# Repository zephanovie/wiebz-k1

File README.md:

# WIEBZ-K1
The Beginning of a new brand...WIEBZ (Willed Into Existence By Zephan).....its a 60% keyboard with a cool design (i hope)
it uses a raspberry pi pico as the MCU, the switches would be hot swappable. it has a daisy chain of SK6812 mini-e leds that would be both bottom mounted for the per key led and top mounted that would serve as the ambient lights around three corners of the keyboard...and it would be running the qmk firmware. The PCB was designed in KiCad, the case in Fusion 

# Features <br><br>
- Rp2040 controller
- per-key led
- a 60% layout
- under glow lights
- qmk firmware

# BOM

| Item                          | Qty       | Price (₦)              | Price($)           | Source                                                                                                                                                                                                                                                                                                                                                                                                                                                                                                                                                                                                                                                                                                                                                               | 
| :---------------------------- | :-------- | :--------------------- | :----------------- | :------------------------------------------------------------------------------------------------------------------------------------------------------------------------------------------------------------------------------------------------------------------------------------------------------------------------------------------------------------------------------------------------------------------------------------------------------------------------------------------------------------------------------------------------------------------------------------------------------------------------------------------------------------------------------------------------------------------------------------------------------------------- | 
| PCB                           | 5         | 48,964.14              | 36.87 (W Shipping) | JLCPCB                                                                                                                                                                                                                                                                                                                                                                                                                                                                                                                                                                                                                                                                                                                                                               | 
| Raspberry Pi Pico W           | 1         | 23,000                 | 17.32              | https://hub360.cc/shop/0408-raspberry-pi-pico-w-rp2040-type-c-dual-core-microcontroller-development-board-12216                                                                                                                                                                                                                                                                                                                                                                                                                                                                                                                                                                                                                                                      | 
| Kailh Hotswappable MX Sockets | 70        | 8,237                  | 6.2                | https://www.aliexpress.com/item/1005012011087592.html?spm=a2g0o.productlist.main.19.23687332bLHZxK&algo_pvid=e4fd706c-1c1c-4431-b9ec-5773bd71d8b5&algo_exp_id=e4fd706c-1c1c-4431-b9ec-5773bd71d8b5-18&pdp_ext_f=%7B%22order%22%3A%223368%22%2C%22eval%22%3A%221%22%2C%22orig_sl_item_id%22%3A%221005012011087592%22%2C%22orig_item_id%22%3A%221005009794038277%22%2C%22fromPage%22%3A%22search%22%7D&pdp_npi=6%40dis%21NGN%2116474.42%218237.00%21%21%2173.78%2136.89%21%40214134eb17905273223806978e0c4b%2112000057272683072%21sea%21NG%217964375220%21X%211%210%21n_tag%3A-29911%3Bd%3Af57d49e4%3Bm03_new_user%3A-29895&curPageLogUid=ZSE8mI1xv3yo&utparam-url=scene%3Asearch%7Cquery_from%3A%7Cx_object_id%3A1005012011087592%7C_p_origin_prod%3A1005009794038277 | 
| MX Mechanical Switches        | 70 (10*7) | 22,967.57 (W Shipping) | 17.29              | https://www.aliexpress.com/item/1005003206504286.html?spm=a2g0o.productlist.main.3.b8f41654VLycgA&algo_pvid=f2801b0d-82a7-46ab-8a0e-5c219dedf416&algo_exp_id=f2801b0d-82a7-46ab-8a0e-5c219dedf416-2&pdp_ext_f=%7B%22order%22%3A%22182%22%2C%22spu_best_type%22%3A%22price%22%2C%22eval%22%3A%221%22%2C%22fromPage%22%3A%22search%22%7D&pdp_npi=6%40dis%21NGN%213192.96%212267.00%21%21%2114.30%2110.15%21%400b08c0c217905277692458720e0f04%2112000024658535533%21sea%21NG%217964375220%21X%211%210%21n_tag%3A-29911%3Bd%3Af57d49e4%3Bm03_new_user%3A-29895&curPageLogUid=cNFM0hmjKg5j&utparam-url=scene%3Asearch%7Cquery_from%3A%7Cx_object_id%3A1005003206504286%7C_p_origin_prod%3A                                                                                | 
| 1N4148 THT Diodes             | 100       | 2,207                  | 1.66               | https://www.aliexpress.com/item/4001126137167.html?spm=a2g0o.productlist.main.2.4cfb37b6KyUXtS&algo_pvid=093f6531-d1bc-4cf5-8007-ee3db067eeed&algo_exp_id=093f6531-d1bc-4cf5-8007-ee3db067eeed-1&pdp_ext_f=%7B%22order%22%3A%222116%22%2C%22spu_best_type%22%3A%22price%22%2C%22eval%22%3A%221%22%2C%22fromPage%22%3A%22search%22%7D&pdp_npi=6%40dis%21NGN%212207.00%212207.00%21%21%211.47%211.47%21%402141397017905286836131318e0ca7%2110000014629985518%21sea%21NG%217964375220%21X%211%210%21n_tag%3A-29911%3Bd%3Af57d49e4%3Bm03_new_user%3A-29895&curPageLogUid=Fgjax7A3c4sT&utparam-url=scene%3Asearch%7Cquery_from%3A%7Cx_object_id%3A4001126137167%7C_p_origin_prod%3A                                                                                       | 
| Stabilizers                   | 5         | 14,321                 | 10.78              | https://www.aliexpress.com/item/4001143514438.html?spm=a2g0o.productlist.main.1.180c40f0HGmRfm&algo_pvid=68c55ac8-eff4-44c4-b19f-65739acc819b&algo_exp_id=68c55ac8-eff4-44c4-b19f-65739acc819b-0&pdp_ext_f=%7B%22order%22%3A%22129%22%2C%22eval%22%3A%221%22%2C%22fromPage%22%3A%22search%22%7D&pdp_npi=6%40dis%21NGN%2113616.00%2113616.00%21%21%219.07%219.07%21%402141137e17905299800648528e0ea6%2112000033301894112%21sea%21NG%217964375220%21X%211%210%21n_tag%3A-29911%3Bd%3Af57d49e4%3Bm03_new_user%3A-29895&curPageLogUid=hGLGjyTulFV4&utparam-url=scene%3Asearch%7Cquery_from%3A%7Cx_object_id%3A4001143514438%7C_p_origin_prod%3A                                                                                                                          | 
| SK6812 MINI-E leds            | 100       | 5,224                  | 3.93               | https://www.aliexpress.com/item/1005007863635868.html?spm=a2g0o.productlist.main.6.14c8547fFrwORl&algo_pvid=d5345fc8-f421-434d-a9b3-912494c1ab0e&algo_exp_id=d5345fc8-f421-434d-a9b3-912494c1ab0e-5&pdp_ext_f=%7B%22order%22%3A%22644%22%2C%22eval%22%3A%221%22%2C%22fromPage%22%3A%22search%22%7D&pdp_npi=6%40dis%21NGN%215224.00%215224.00%21%21%213.48%213.48%21%4021410daa17905379482431718e0f31%2112000042594617264%21sea%21NG%217964375220%21X%211%210%21n_tag%3A-29911%3Bd%3Af57d49e4%3Bm03_new_user%3A-29895&curPageLogUid=zBx0bm7r2RNj&utparam-url=scene%3Asearch%7Cquery_from%3A%7Cx_object_id%3A1005007863635868%7C_p_origin_prod%3A                                                                                                                      | 
| Screws                        | 0         | 0                      | 0                  | Self-Covered                                                                                                                                                                                                                                                                                                                                                                                                                                                                                                                                                                                                                                                                                                                                                         | 
| Heat Inserts                  | 0         | 0                      | 0                  | Self-Covered                                                                                                                                                                                                                                                                                                                                                                                                                                                                                                                                                                                                                                                                                                                                                         | 
| Key Caps                      | 133 keys  | 19,885                 | 14.97              | https://www.aliexpress.com/item/1005009592262575.html?spm=a2g0o.productlist.main.2.711f3e457cKNiY&algo_pvid=7fbda4a7-b7a8-44b1-97d1-95525804c150&algo_exp_id=7fbda4a7-b7a8-44b1-97d1-95525804c150-1&pdp_ext_f=%7B%22order%22%3A%22369%22%2C%22spu_best_type%22%3A%22price%22%2C%22eval%22%3A%221%22%2C%22fromPage%22%3A%22search%22%7D&pdp_npi=6%40dis%21NGN%2141427.08%2119885.00%21%21%21185.52%2189.05%21%400be71e1917905404057533196e0c73%2112000049561056701%21sea%21NG%217964375220%21X%211%210%21n_tag%3A-29911%3Bd%3Af57d49e4%3Bm03_new_user%3A-29895&curPageLogUid=Qs7ffMCvOio6&utparam-url=scene%3Asearch%7Cquery_from%3A%7Cx_object_id%3A1005009592262575%7C_p_origin_prod%3A                                                                             | 
| TOTAL                         |           | 121,838.14             | 72.15              |                                                                                                                                                                                                                                                                                                                                                                                                                                                                                                                                                                                                                                                                                                                                                                      | 

# Images
## Schematics
#### Keyboard Matrix

#### LED Chain

#### MCU

## PCB
#### PCB Design

#### PCB 3D Render

## Case
#### Plate

#### Base

### MCU Cover
 (to be glue to the plate after printing)

#### Full Case

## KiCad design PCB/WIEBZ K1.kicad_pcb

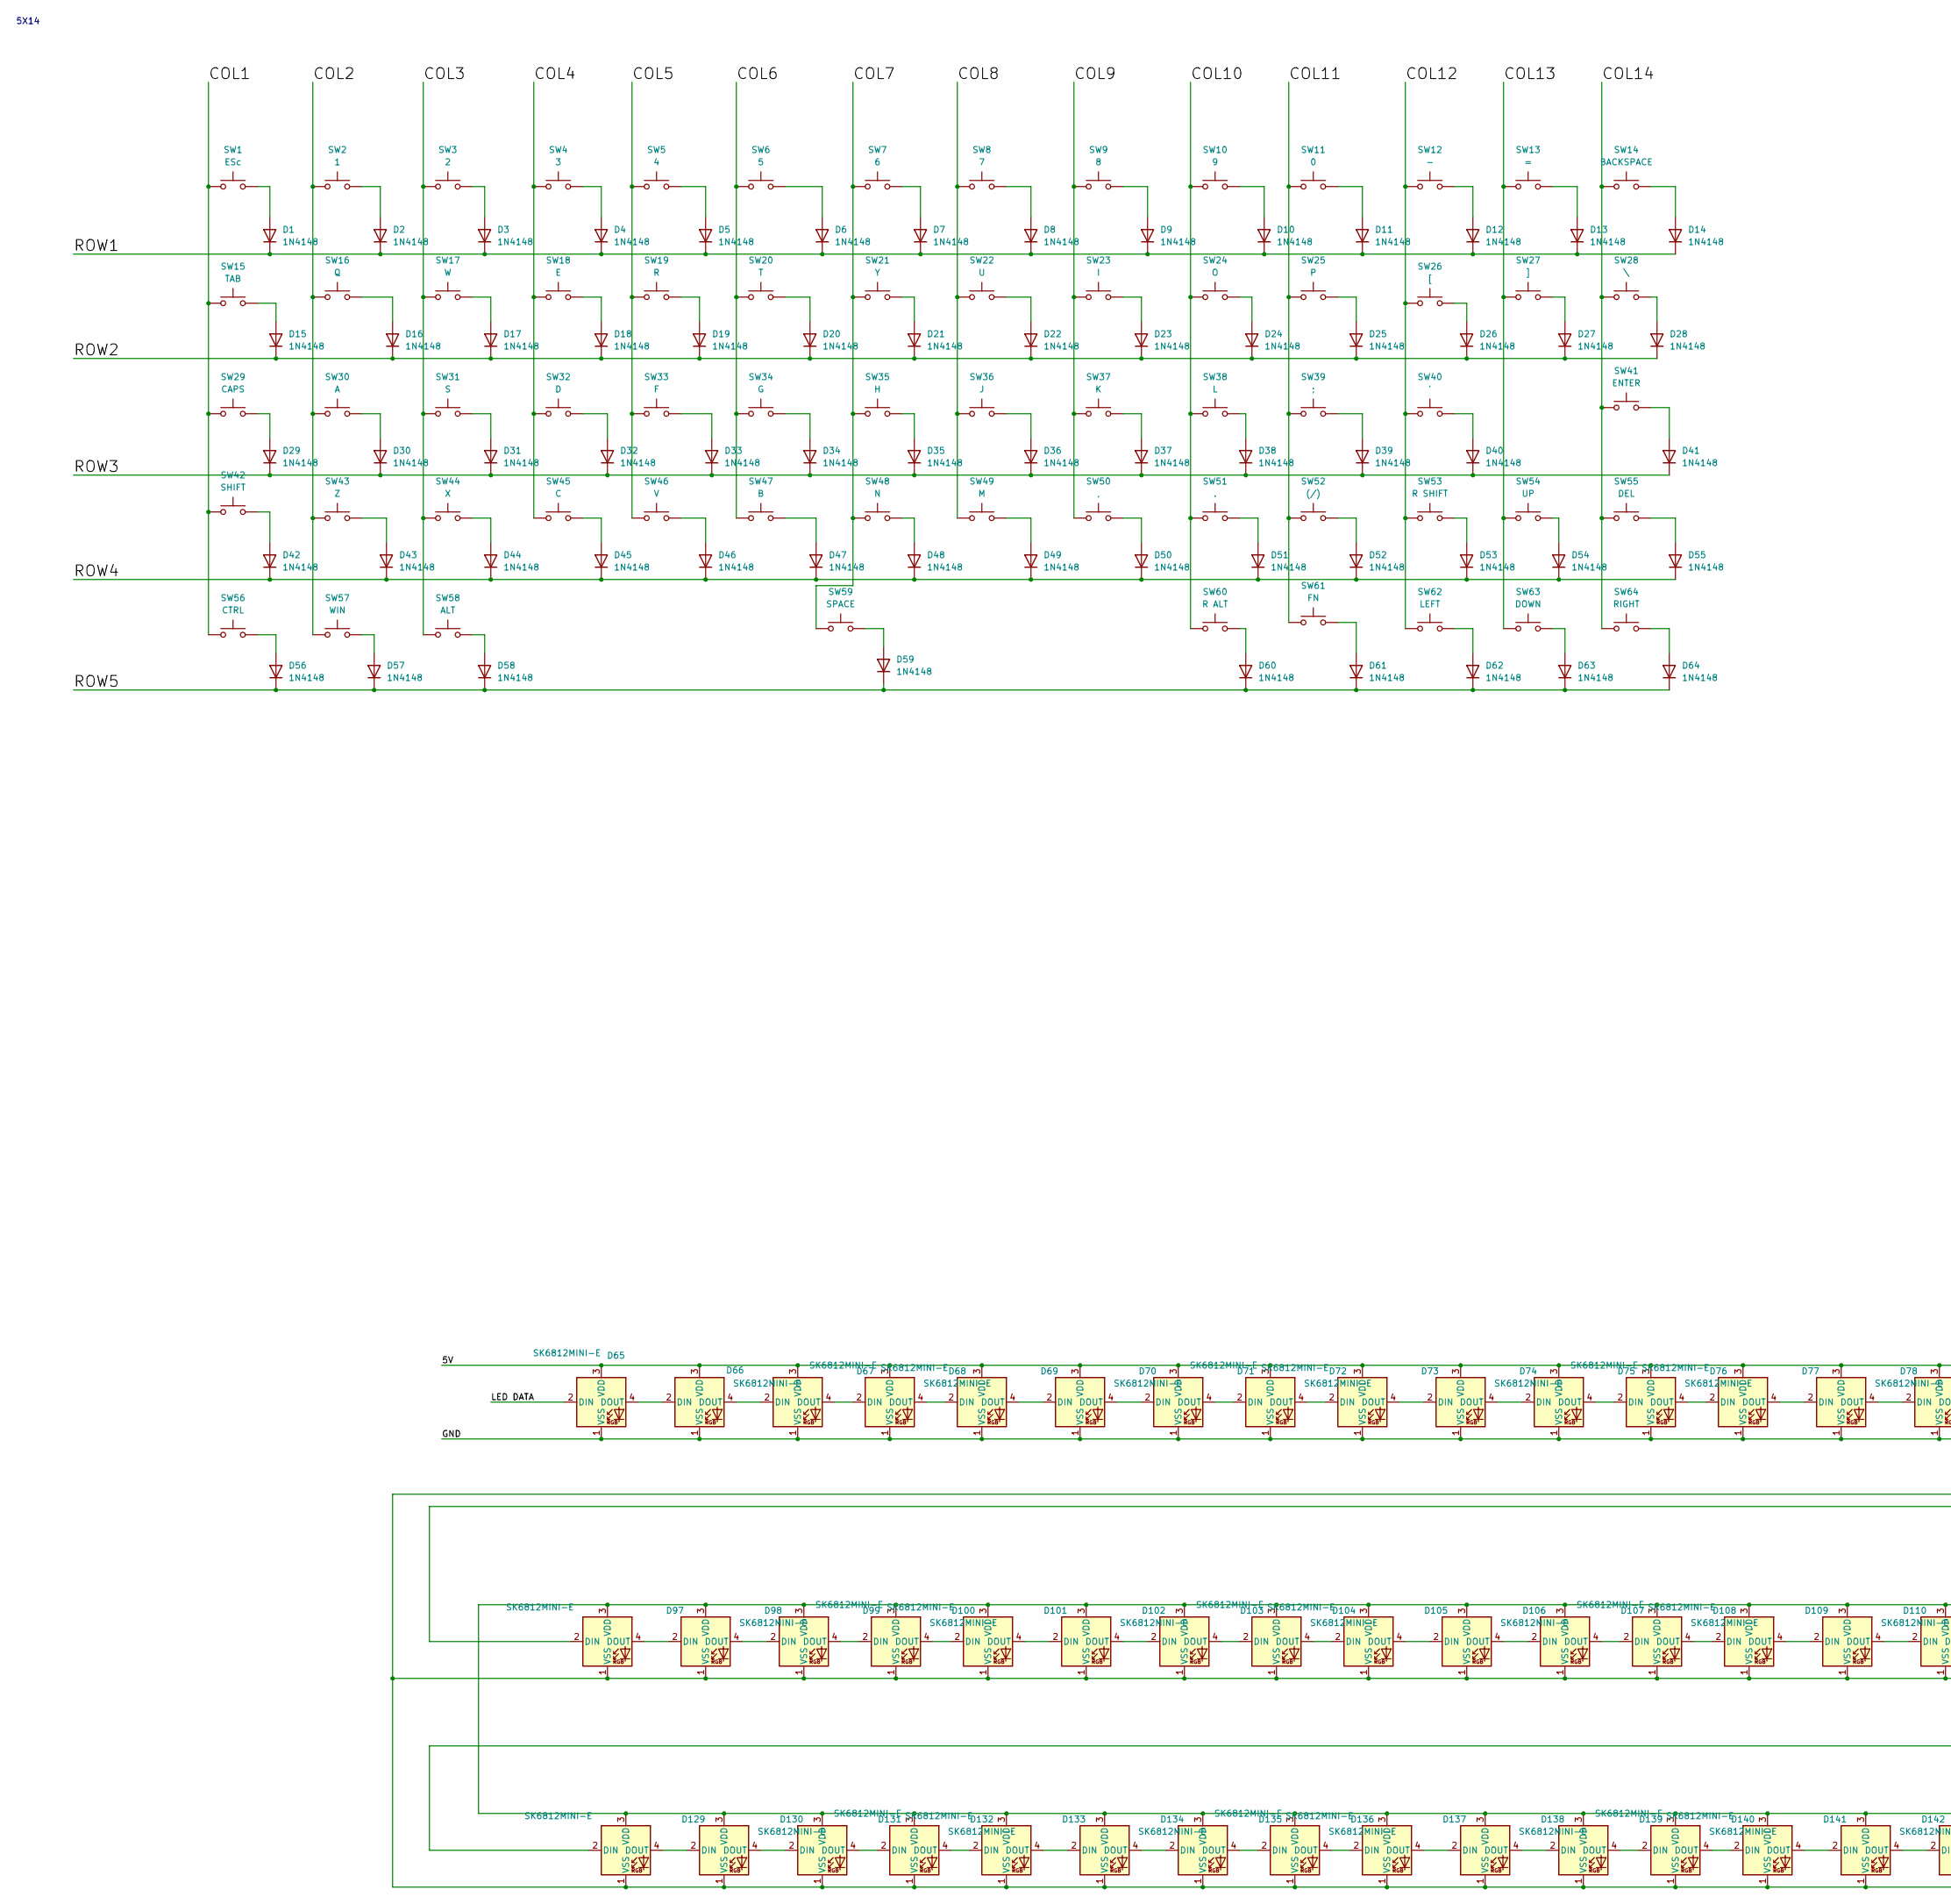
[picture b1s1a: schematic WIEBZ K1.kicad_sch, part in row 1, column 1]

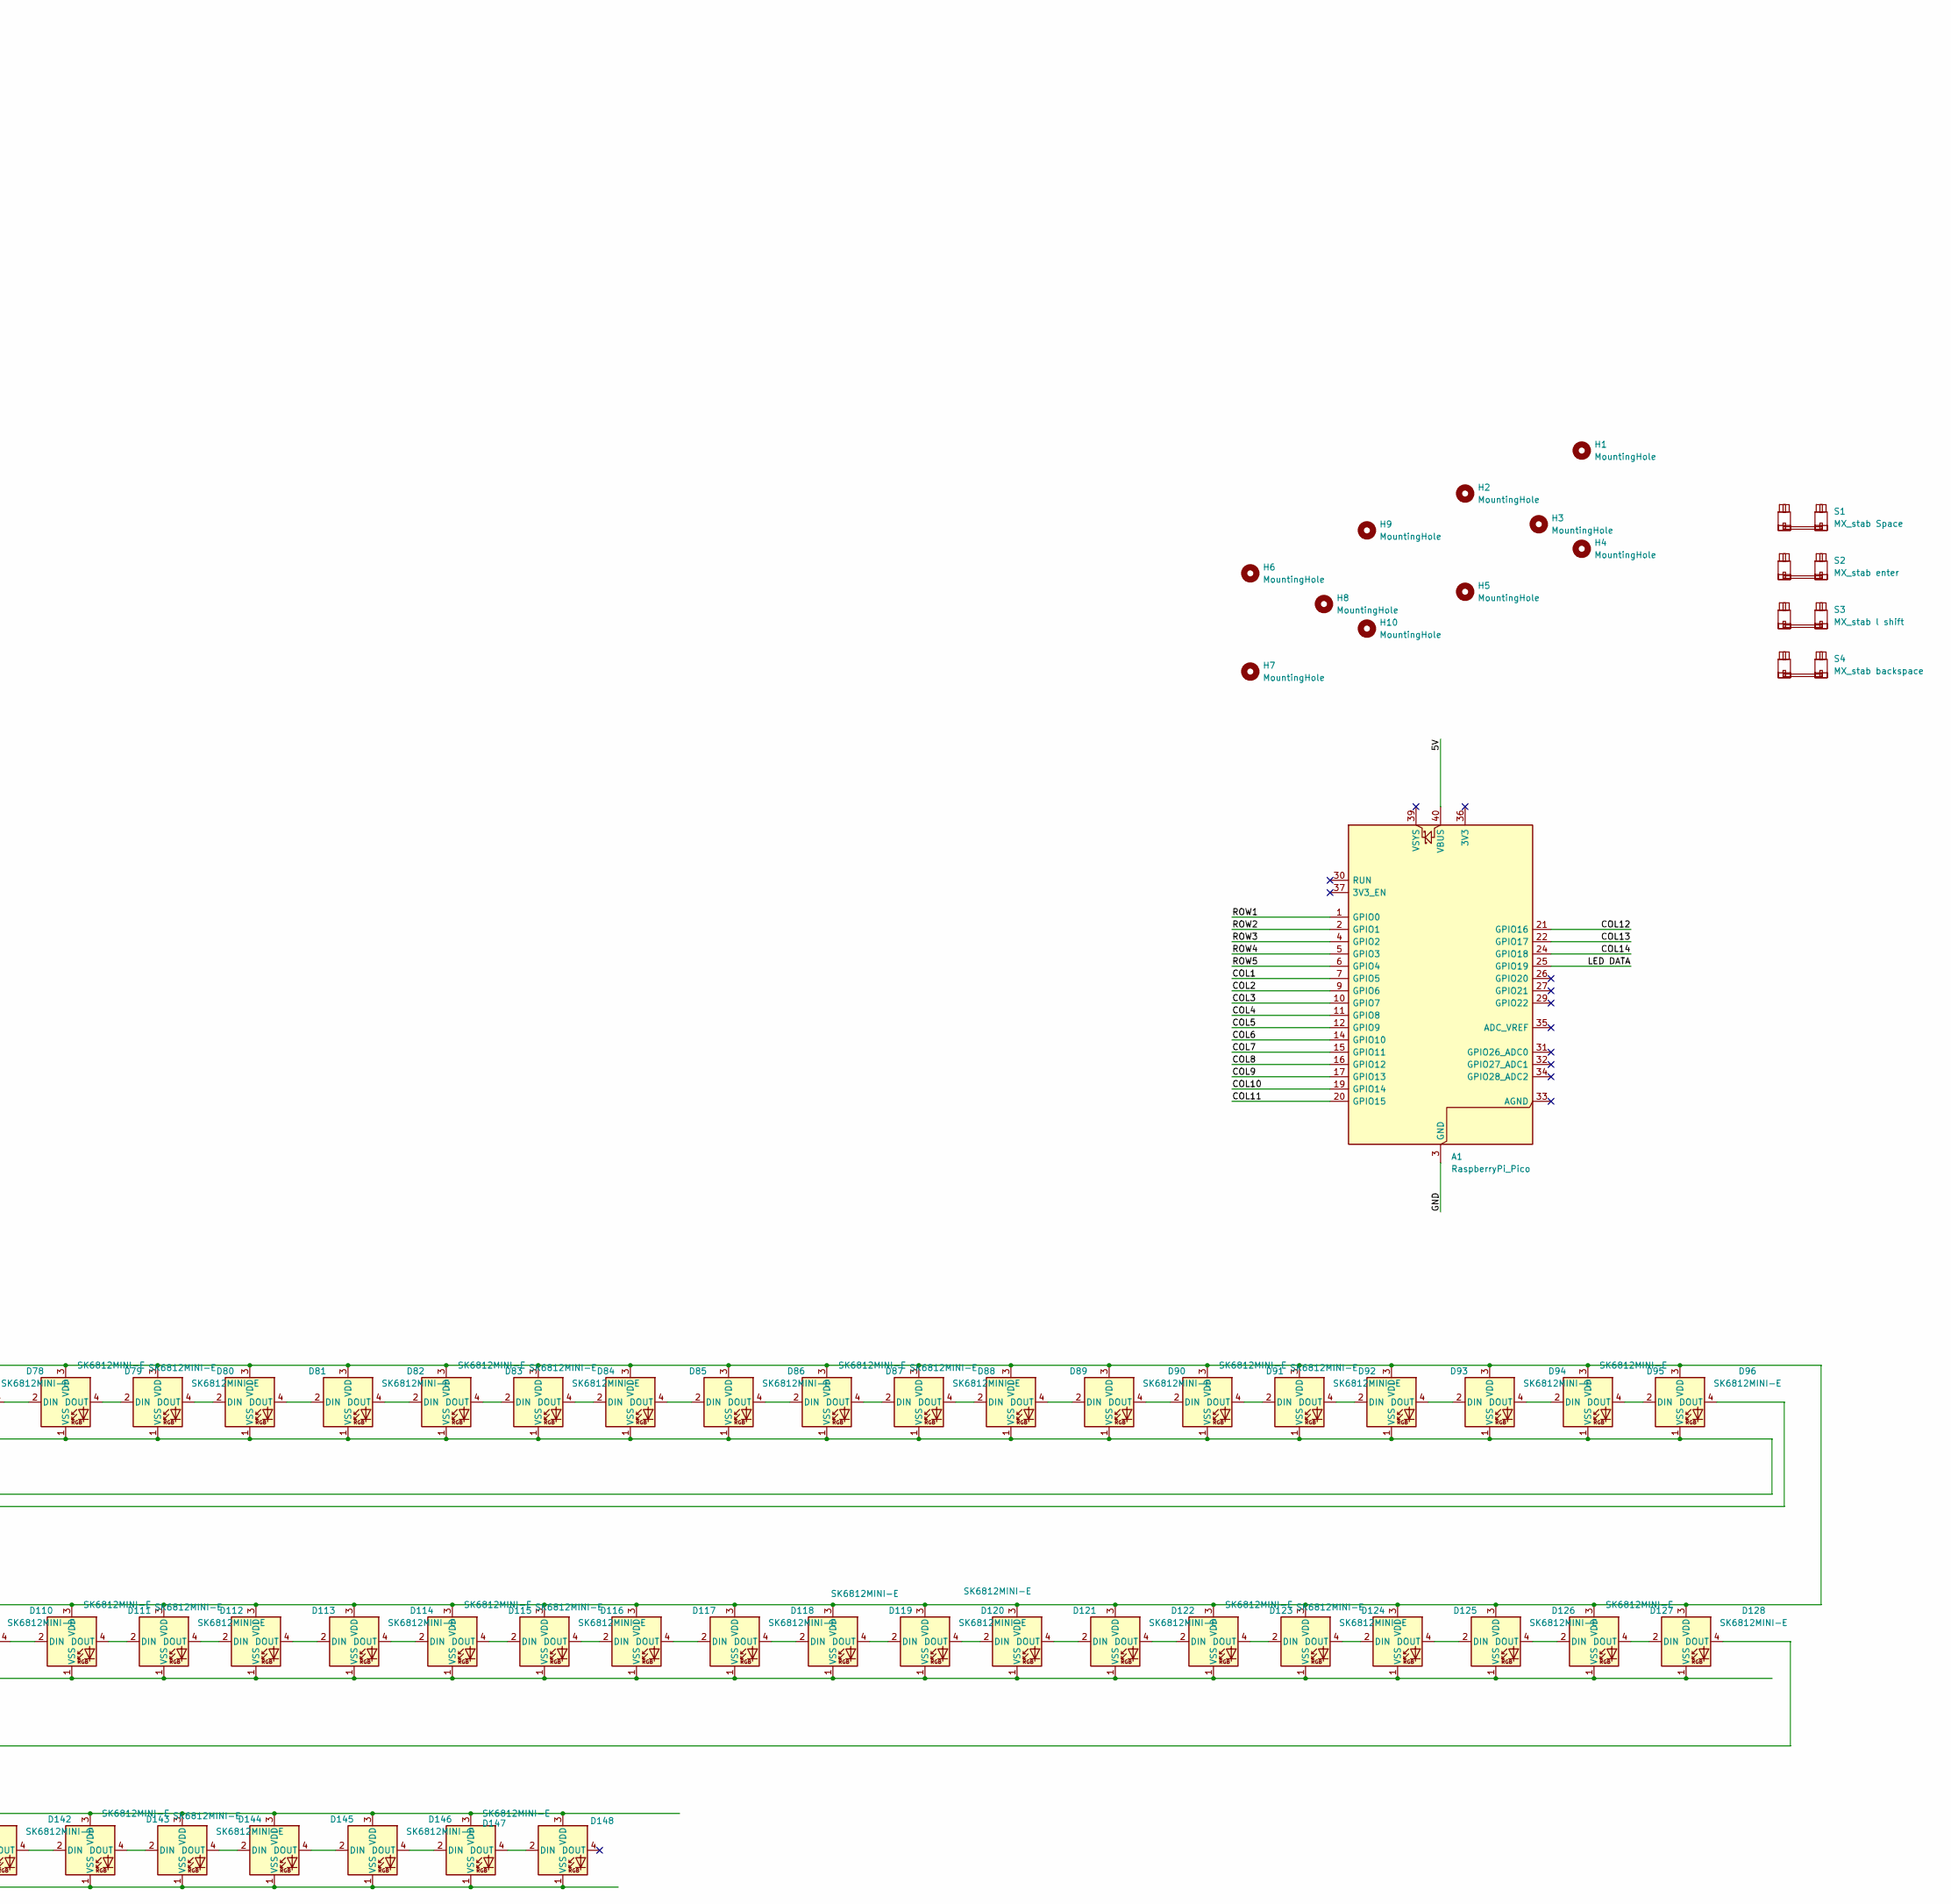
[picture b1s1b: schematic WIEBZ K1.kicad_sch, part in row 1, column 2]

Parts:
A1: RaspberryPi_Pico; RaspberryPi_Pico_Common_THT
D1, D2, D3, D4, D5, D6, D7, D8, D9, D10, D11, D12, D13, D14, D15, D16, D17, D18, D19, D20, D21, D22, D23, D24, D25, D26, D27, D28, D29, D30, D31, D32, D33, D34, D35, D36, D37, D38, D39, D40, D41, D42, D43, D44, D45, D46, D47, D48, D49, D50, D51, D52, D53, D54, D55, D56, D57, D58, D59, D60, D61, D62, D63, D64: 1N4148; D_DO-35_SOD27_P7.62mm_Horizontal
D65, D66, D67, D68, D69, D70, D71, D72, D73, D74, D75, D76, D77, D78, D79, D80, D81, D82, D83, D84, D85, D86, D87, D88, D89, D90, D91, D92, D93, D94, D95, D96, D97, D98, D99, D100, D101, D102, D103, D104, D105, D106, D107, D108, D109, D110, D111, D112, D113, D114, D115, D116, D117, D118, D119, D120, D121, D122, D123, D124, D125, D126, D127, D128, D129, D130, D131, D132, D133, D134, D135, D136, D137, D138, D139, D140, D141, D142, D143, D144, D145, D146, D147, D148: SK6812MINI-E; LED_SK6812MINI-E_3.2x2.8mm_P1.5mm_ReverseMount
H1, H2, H3, H4, H5, H6, H7, H8, H9, H10: MountingHole; MountingHole_3.2mm_M3
S1: MX_stab Space; STAB_MX_6.25u
S2: MX_stab enter; STAB_MX_2.25u
S3: MX_stab l shift; STAB_MX_2u
S4: MX_stab backspace; STAB_MX_2u
SW1: ESc; SW_Hotswap_Kailh_MX_1.00u_No_silk
SW2: 1; SW_Hotswap_Kailh_MX_1.00u_No_silk
SW3: 2; SW_Hotswap_Kailh_MX_1.00u_No_silk
SW4: 3; SW_Hotswap_Kailh_MX_1.00u_No_silk
SW5: 4; SW_Hotswap_Kailh_MX_1.00u_No_silk
SW6: 5; SW_Hotswap_Kailh_MX_1.00u_No_silk
SW7: 6; SW_Hotswap_Kailh_MX_1.00u_No_silk
SW8: 7; SW_Hotswap_Kailh_MX_1.00u_No_silk
SW9: 8; SW_Hotswap_Kailh_MX_1.00u_No_silk
SW10: 9; SW_Hotswap_Kailh_MX_1.00u_No_silk
SW11: 0; SW_Hotswap_Kailh_MX_1.00u_No_silk
SW12: -; SW_Hotswap_Kailh_MX_1.00u_No_silk
SW13: =; SW_Hotswap_Kailh_MX_1.00u_No_silk
SW14: BACKSPACE; SW_Hotswap_Kailh_MX_1.00u_No_silk
SW15: TAB; SW_Hotswap_Kailh_MX_1.00u_No_silk
SW16: Q; SW_Hotswap_Kailh_MX_1.00u_No_silk
SW17: W; SW_Hotswap_Kailh_MX_1.00u_No_silk
SW18: E; SW_Hotswap_Kailh_MX_1.00u_No_silk
SW19: R; SW_Hotswap_Kailh_MX_1.00u_No_silk
SW20: T; SW_Hotswap_Kailh_MX_1.00u_No_silk
SW21: Y; SW_Hotswap_Kailh_MX_1.00u_No_silk
SW22: U; SW_Hotswap_Kailh_MX_1.00u_No_silk
SW23: I; SW_Hotswap_Kailh_MX_1.00u_No_silk
SW24: O; SW_Hotswap_Kailh_MX_1.00u_No_silk
SW25: P; SW_Hotswap_Kailh_MX_1.00u_No_silk
SW26: [; SW_Hotswap_Kailh_MX_1.00u_No_silk
SW27: ]; SW_Hotswap_Kailh_MX_1.00u_No_silk
SW28: \; SW_Hotswap_Kailh_MX_1.00u_No_silk
SW29: CAPS; SW_Hotswap_Kailh_MX_1.00u_No_silk
SW30: A; SW_Hotswap_Kailh_MX_1.00u_No_silk
SW31: S; SW_Hotswap_Kailh_MX_1.00u_No_silk
SW32: D; SW_Hotswap_Kailh_MX_1.00u_No_silk
SW33: F; SW_Hotswap_Kailh_MX_1.00u_No_silk
SW34: G; SW_Hotswap_Kailh_MX_1.00u_No_silk
SW35: H; SW_Hotswap_Kailh_MX_1.00u_No_silk
SW36: J; SW_Hotswap_Kailh_MX_1.00u_No_silk
SW37: K; SW_Hotswap_Kailh_MX_1.00u_No_silk
SW38: L; SW_Hotswap_Kailh_MX_1.00u_No_silk
SW39: ;; SW_Hotswap_Kailh_MX_1.00u_No_silk
SW40: '; SW_Hotswap_Kailh_MX_1.00u_No_silk
SW41: ENTER; SW_Hotswap_Kailh_MX_1.00u_No_silk
SW42: SHIFT; SW_Hotswap_Kailh_MX_1.00u_No_silk
SW43: Z; SW_Hotswap_Kailh_MX_1.00u_No_silk
SW44: X; SW_Hotswap_Kailh_MX_1.00u_No_silk
SW45: C; SW_Hotswap_Kailh_MX_1.00u_No_silk
SW46: V; SW_Hotswap_Kailh_MX_1.00u_No_silk
SW47: B; SW_Hotswap_Kailh_MX_1.00u_No_silk
SW48: N; SW_Hotswap_Kailh_MX_1.00u_No_silk
SW49: M; SW_Hotswap_Kailh_MX_1.00u_No_silk
SW50: ,; SW_Hotswap_Kailh_MX_1.00u_No_silk
SW51: .; SW_Hotswap_Kailh_MX_1.00u_No_silk
SW52: (/); SW_Hotswap_Kailh_MX_1.00u_No_silk
SW53: R SHIFT; SW_Hotswap_Kailh_MX_1.00u_No_silk
SW54: UP; SW_Hotswap_Kailh_MX_1.00u_No_silk
SW55: DEL; SW_Hotswap_Kailh_MX_1.00u_No_silk
SW56: CTRL; SW_Hotswap_Kailh_MX_1.00u_No_silk
SW57: WIN; SW_Hotswap_Kailh_MX_1.00u_No_silk
SW58: ALT; SW_Hotswap_Kailh_MX_1.00u_No_silk
SW59: SPACE; SW_Hotswap_Kailh_MX_1.00u_No_silk
SW60: R ALT; SW_Hotswap_Kailh_MX_1.00u_No_silk
SW61: FN; SW_Hotswap_Kailh_MX_1.00u_No_silk
SW62: LEFT; SW_Hotswap_Kailh_MX_1.00u_No_silk
SW63: DOWN; SW_Hotswap_Kailh_MX_1.00u_No_silk
SW64: RIGHT; SW_Hotswap_Kailh_MX_1.00u_No_silk

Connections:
/5V: A1.40 (VBUS), D65.3 (VDD), D66.3 (VDD), D67.3 (VDD), D68.3 (VDD), D69.3 (VDD), D70.3 (VDD), D71.3 (VDD), D72.3 (VDD), D73.3 (VDD), D74.3 (VDD), D75.3 (VDD), D76.3 (VDD), D77.3 (VDD), D78.3 (VDD), D79.3 (VDD), D80.3 (VDD), D81.3 (VDD), D82.3 (VDD), D83.3 (VDD), D84.3 (VDD), D85.3 (VDD), D86.3 (VDD), D87.3 (VDD), D88.3 (VDD), D89.3 (VDD), D90.3 (VDD), D91.3 (VDD), D92.3 (VDD), D93.3 (VDD), D94.3 (VDD), D95.3 (VDD), D96.3 (VDD), D97.3 (VDD), D98.3 (VDD), D99.3 (VDD), D100.3 (VDD), D101.3 (VDD), D102.3 (VDD), D103.3 (VDD), D104.3 (VDD), D105.3 (VDD), D106.3 (VDD), D107.3 (VDD), D108.3 (VDD), D109.3 (VDD), D110.3 (VDD), D111.3 (VDD), D112.3 (VDD), D113.3 (VDD), D114.3 (VDD), D115.3 (VDD), D116.3 (VDD), D117.3 (VDD), D118.3 (VDD), D119.3 (VDD), D120.3 (VDD), D121.3 (VDD), D122.3 (VDD), D123.3 (VDD), D124.3 (VDD), D125.3 (VDD), D126.3 (VDD), D127.3 (VDD), D128.3 (VDD), D129.3 (VDD), D130.3 (VDD), D131.3 (VDD), D132.3 (VDD), D133.3 (VDD), D134.3 (VDD), D135.3 (VDD), D136.3 (VDD), D137.3 (VDD), D138.3 (VDD), D139.3 (VDD), D140.3 (VDD), D141.3 (VDD), D142.3 (VDD), D143.3 (VDD), D144.3 (VDD), D145.3 (VDD), D146.3 (VDD), D147.3 (VDD), D148.3 (VDD)
/COL1: A1.7 (GPIO5), SW1.1, SW15.1, SW29.1, SW42.1, SW56.1
/COL2: A1.9 (GPIO6), SW2.1, SW16.1, SW30.1, SW43.1, SW57.1
/COL3: A1.10 (GPIO7), SW3.1, SW17.1, SW31.1, SW44.1, SW58.1
/COL4: A1.11 (GPIO8), SW4.1, SW18.1, SW32.1, SW45.1
/COL5: A1.12 (GPIO9), SW5.1, SW19.1, SW33.1, SW46.1
/COL6: A1.14 (GPIO10), SW6.1, SW20.1, SW34.1, SW47.1
/COL7: A1.15 (GPIO11), SW7.1, SW21.1, SW35.1, SW48.1, SW59.1
/COL8: A1.16 (GPIO12), SW8.1, SW22.1, SW36.1, SW49.1
/COL9: A1.17 (GPIO13), SW9.1, SW23.1, SW37.1, SW50.1
/COL10: A1.19 (GPIO14), SW10.1, SW24.1, SW38.1, SW51.1, SW60.1
/COL11: A1.20 (GPIO15), SW11.1, SW25.1, SW39.1, SW52.1, SW61.1
/COL12: A1.21 (GPIO16), SW12.1, SW26.1, SW40.1, SW53.1, SW62.1
/COL13: A1.22 (GPIO17), SW13.1, SW27.1, SW54.1, SW63.1
/COL14: A1.24 (GPIO18), SW14.1, SW28.1, SW41.1, SW55.1, SW64.1
/GND: A1.3 (GND), A1.8 (GND), A1.13 (GND), A1.18 (GND), A1.23 (GND), A1.28 (GND), A1.38 (GND), D65.1 (VSS), D66.1 (VSS), D67.1 (VSS), D68.1 (VSS), D69.1 (VSS), D70.1 (VSS), D71.1 (VSS), D72.1 (VSS), D73.1 (VSS), D74.1 (VSS), D75.1 (VSS), D76.1 (VSS), D77.1 (VSS), D78.1 (VSS), D79.1 (VSS), D80.1 (VSS), D81.1 (VSS), D82.1 (VSS), D83.1 (VSS), D84.1 (VSS), D85.1 (VSS), D86.1 (VSS), D87.1 (VSS), D88.1 (VSS), D89.1 (VSS), D90.1 (VSS), D91.1 (VSS), D92.1 (VSS), D93.1 (VSS), D94.1 (VSS), D95.1 (VSS), D96.1 (VSS), D97.1 (VSS), D98.1 (VSS), D99.1 (VSS), D100.1 (VSS), D101.1 (VSS), D102.1 (VSS), D103.1 (VSS), D104.1 (VSS), D105.1 (VSS), D106.1 (VSS), D107.1 (VSS), D108.1 (VSS), D109.1 (VSS), D110.1 (VSS), D111.1 (VSS), D112.1 (VSS), D113.1 (VSS), D114.1 (VSS), D115.1 (VSS), D116.1 (VSS), D117.1 (VSS), D118.1 (VSS), D119.1 (VSS), D120.1 (VSS), D121.1 (VSS), D122.1 (VSS), D123.1 (VSS), D124.1 (VSS), D125.1 (VSS), D126.1 (VSS), D127.1 (VSS), D128.1 (VSS), D129.1 (VSS), D130.1 (VSS), D131.1 (VSS), D132.1 (VSS), D133.1 (VSS), D134.1 (VSS), D135.1 (VSS), D136.1 (VSS), D137.1 (VSS), D138.1 (VSS), D139.1 (VSS), D140.1 (VSS), D141.1 (VSS), D142.1 (VSS), D143.1 (VSS), D144.1 (VSS), D145.1 (VSS), D146.1 (VSS), D147.1 (VSS), D148.1 (VSS)
/LED DATA: A1.25 (GPIO19), D65.2 (DIN)
/ROW1: A1.1 (GPIO0), D1.1 (K), D2.1 (K), D3.1 (K), D4.1 (K), D5.1 (K), D6.1 (K), D7.1 (K), D8.1 (K), D9.1 (K), D10.1 (K), D11.1 (K), D12.1 (K), D13.1 (K), D14.1 (K)
/ROW2: A1.2 (GPIO1), D15.1 (K), D16.1 (K), D17.1 (K), D18.1 (K), D19.1 (K), D20.1 (K), D21.1 (K), D22.1 (K), D23.1 (K), D24.1 (K), D25.1 (K), D26.1 (K), D27.1 (K), D28.1 (K)
/ROW3: A1.4 (GPIO2), D29.1 (K), D30.1 (K), D31.1 (K), D32.1 (K), D33.1 (K), D34.1 (K), D35.1 (K), D36.1 (K), D37.1 (K), D38.1 (K), D39.1 (K), D40.1 (K), D41.1 (K)
/ROW4: A1.5 (GPIO3), D42.1 (K), D43.1 (K), D44.1 (K), D45.1 (K), D46.1 (K), D47.1 (K), D48.1 (K), D49.1 (K), D50.1 (K), D51.1 (K), D52.1 (K), D53.1 (K), D54.1 (K), D55.1 (K)
/ROW5: A1.6 (GPIO4), D56.1 (K), D57.1 (K), D58.1 (K), D59.1 (K), D60.1 (K), D61.1 (K), D62.1 (K), D63.1 (K), D64.1 (K)
unnamed: D1.2 (A), SW1.2
unnamed: D2.2 (A), SW2.2
unnamed: D3.2 (A), SW3.2
unnamed: D4.2 (A), SW4.2
unnamed: D5.2 (A), SW5.2
unnamed: D6.2 (A), SW6.2
unnamed: D7.2 (A), SW7.2
unnamed: D8.2 (A), SW8.2
unnamed: D9.2 (A), SW9.2
unnamed: D10.2 (A), SW10.2
unnamed: D11.2 (A), SW11.2
unnamed: D12.2 (A), SW12.2
unnamed: D13.2 (A), SW13.2
unnamed: D14.2 (A), SW14.2
unnamed: D15.2 (A), SW15.2
unnamed: D16.2 (A), SW16.2
unnamed: D17.2 (A), SW17.2
unnamed: D18.2 (A), SW18.2
unnamed: D19.2 (A), SW19.2
unnamed: D20.2 (A), SW20.2
unnamed: D21.2 (A), SW21.2
unnamed: D22.2 (A), SW22.2
unnamed: D23.2 (A), SW23.2
unnamed: D24.2 (A), SW24.2
unnamed: D25.2 (A), SW25.2
unnamed: D26.2 (A), SW26.2
unnamed: D27.2 (A), SW27.2
unnamed: D28.2 (A), SW28.2
unnamed: D29.2 (A), SW29.2
unnamed: D30.2 (A), SW30.2
unnamed: D31.2 (A), SW31.2
unnamed: D32.2 (A), SW32.2
unnamed: D33.2 (A), SW33.2
unnamed: D34.2 (A), SW34.2
unnamed: D35.2 (A), SW35.2
unnamed: D36.2 (A), SW36.2
unnamed: D37.2 (A), SW37.2
unnamed: D38.2 (A), SW38.2
unnamed: D39.2 (A), SW39.2
unnamed: D40.2 (A), SW40.2
unnamed: D41.2 (A), SW41.2
unnamed: D42.2 (A), SW42.2
unnamed: D43.2 (A), SW43.2
unnamed: D44.2 (A), SW44.2
unnamed: D45.2 (A), SW45.2
unnamed: D46.2 (A), SW46.2
unnamed: D47.2 (A), SW47.2
unnamed: D48.2 (A), SW48.2
unnamed: D49.2 (A), SW49.2
unnamed: D50.2 (A), SW50.2
unnamed: D51.2 (A), SW51.2
unnamed: D52.2 (A), SW52.2
unnamed: D53.2 (A), SW53.2
unnamed: D54.2 (A), SW54.2
unnamed: D55.2 (A), SW55.2
unnamed: D56.2 (A), SW56.2
unnamed: D57.2 (A), SW57.2
unnamed: D58.2 (A), SW58.2
unnamed: D59.2 (A), SW59.2
unnamed: D60.2 (A), SW60.2
unnamed: D61.2 (A), SW61.2
unnamed: D62.2 (A), SW62.2
unnamed: D63.2 (A), SW63.2
unnamed: D64.2 (A), SW64.2
unnamed: D65.4 (DOUT), D66.2 (DIN)
unnamed: D66.4 (DOUT), D67.2 (DIN)
unnamed: D67.4 (DOUT), D68.2 (DIN)
unnamed: D68.4 (DOUT), D69.2 (DIN)
unnamed: D69.4 (DOUT), D70.2 (DIN)
unnamed: D70.4 (DOUT), D71.2 (DIN)
unnamed: D71.4 (DOUT), D72.2 (DIN)
unnamed: D72.4 (DOUT), D73.2 (DIN)
unnamed: D73.4 (DOUT), D74.2 (DIN)
unnamed: D74.4 (DOUT), D75.2 (DIN)
unnamed: D75.4 (DOUT), D76.2 (DIN)
unnamed: D76.4 (DOUT), D77.2 (DIN)
unnamed: D77.4 (DOUT), D78.2 (DIN)
unnamed: D78.4 (DOUT), D79.2 (DIN)
unnamed: D79.4 (DOUT), D80.2 (DIN)
unnamed: D80.4 (DOUT), D81.2 (DIN)
unnamed: D81.4 (DOUT), D82.2 (DIN)
unnamed: D82.4 (DOUT), D83.2 (DIN)
unnamed: D83.4 (DOUT), D84.2 (DIN)
unnamed: D84.4 (DOUT), D85.2 (DIN)
unnamed: D85.4 (DOUT), D86.2 (DIN)
unnamed: D86.4 (DOUT), D87.2 (DIN)
unnamed: D87.4 (DOUT), D88.2 (DIN)
unnamed: D88.4 (DOUT), D89.2 (DIN)
unnamed: D89.4 (DOUT), D90.2 (DIN)
unnamed: D90.4 (DOUT), D91.2 (DIN)
unnamed: D91.4 (DOUT), D92.2 (DIN)
unnamed: D92.4 (DOUT), D93.2 (DIN)
unnamed: D93.4 (DOUT), D94.2 (DIN)
unnamed: D94.4 (DOUT), D95.2 (DIN)
unnamed: D95.4 (DOUT), D96.2 (DIN)
unnamed: D96.4 (DOUT), D97.2 (DIN)
unnamed: D97.4 (DOUT), D98.2 (DIN)
unnamed: D98.4 (DOUT), D99.2 (DIN)
unnamed: D99.4 (DOUT), D100.2 (DIN)
unnamed: D100.4 (DOUT), D101.2 (DIN)
unnamed: D101.4 (DOUT), D102.2 (DIN)
unnamed: D102.4 (DOUT), D103.2 (DIN)
unnamed: D103.4 (DOUT), D104.2 (DIN)
unnamed: D104.4 (DOUT), D105.2 (DIN)
unnamed: D105.4 (DOUT), D106.2 (DIN)
unnamed: D106.4 (DOUT), D107.2 (DIN)
unnamed: D107.4 (DOUT), D108.2 (DIN)
unnamed: D108.4 (DOUT), D109.2 (DIN)
unnamed: D109.4 (DOUT), D110.2 (DIN)
unnamed: D110.4 (DOUT), D111.2 (DIN)
unnamed: D111.4 (DOUT), D112.2 (DIN)
unnamed: D112.4 (DOUT), D113.2 (DIN)
unnamed: D113.4 (DOUT), D114.2 (DIN)
unnamed: D114.4 (DOUT), D115.2 (DIN)
unnamed: D115.4 (DOUT), D116.2 (DIN)
unnamed: D116.4 (DOUT), D117.2 (DIN)
unnamed: D117.4 (DOUT), D118.2 (DIN)
unnamed: D118.4 (DOUT), D119.2 (DIN)
unnamed: D119.4 (DOUT), D120.2 (DIN)
unnamed: D120.4 (DOUT), D121.2 (DIN)
unnamed: D121.4 (DOUT), D122.2 (DIN)
unnamed: D122.4 (DOUT), D123.2 (DIN)
unnamed: D123.4 (DOUT), D124.2 (DIN)
unnamed: D124.4 (DOUT), D125.2 (DIN)
unnamed: D125.4 (DOUT), D126.2 (DIN)
unnamed: D126.4 (DOUT), D127.2 (DIN)
unnamed: D127.4 (DOUT), D128.2 (DIN)
unnamed: D128.4 (DOUT), D129.2 (DIN)
unnamed: D129.4 (DOUT), D130.2 (DIN)
unnamed: D130.4 (DOUT), D131.2 (DIN)
unnamed: D131.4 (DOUT), D132.2 (DIN)
unnamed: D132.4 (DOUT), D133.2 (DIN)
unnamed: D133.4 (DOUT), D134.2 (DIN)
unnamed: D134.4 (DOUT), D135.2 (DIN)
unnamed: D135.4 (DOUT), D136.2 (DIN)
unnamed: D136.4 (DOUT), D137.2 (DIN)
unnamed: D137.4 (DOUT), D138.2 (DIN)
unnamed: D138.4 (DOUT), D139.2 (DIN)
unnamed: D139.4 (DOUT), D140.2 (DIN)
unnamed: D140.4 (DOUT), D141.2 (DIN)
unnamed: D141.4 (DOUT), D142.2 (DIN)
unnamed: D142.4 (DOUT), D143.2 (DIN)
unnamed: D143.4 (DOUT), D144.2 (DIN)
unnamed: D144.4 (DOUT), D145.2 (DIN)
unnamed: D145.4 (DOUT), D146.2 (DIN)
unnamed: D146.4 (DOUT), D147.2 (DIN)
unnamed: D147.4 (DOUT), D148.2 (DIN)

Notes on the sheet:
5X14

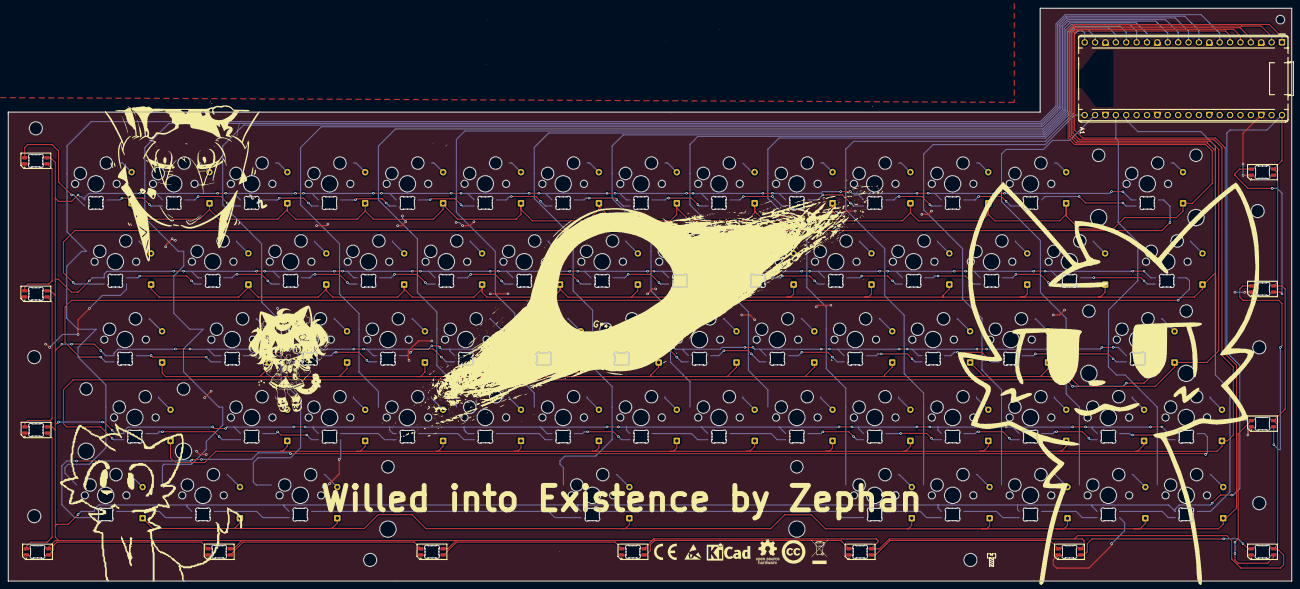
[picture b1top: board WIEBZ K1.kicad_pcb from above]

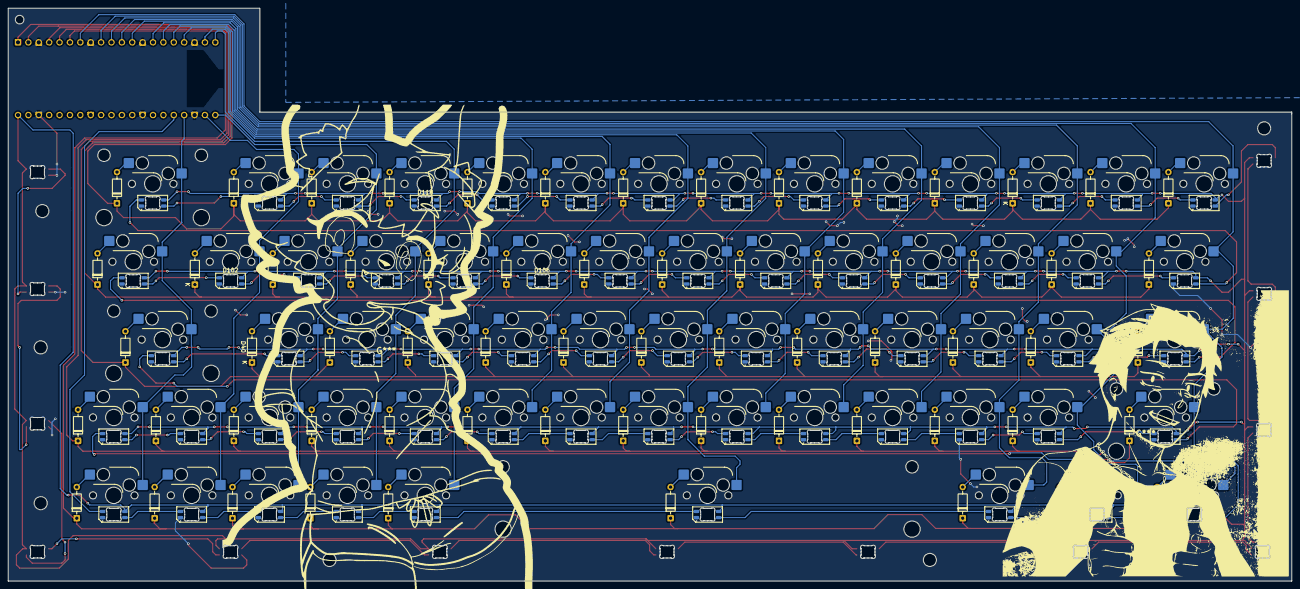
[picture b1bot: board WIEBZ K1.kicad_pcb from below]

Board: 2 copper layers, 313.9 x 140.1 mm, 218 parts (128 on the bottom side), 162 nets.
